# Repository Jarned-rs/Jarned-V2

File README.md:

# Jarned-V2
An improvement on the Jarned V1. A whole spilt keyboard with bluetooth!
I made it as a way to challenge myself after V1!

# Features
- 2 XIAO microcontrollers to control both sides
- 40 Keys!
- Bluetooth connectivity
- An open concept case to be able to marvel at the raw PCB
- 40 Diodes
- ZMK firmware to connect the two

# Photos!

# BOM
| Item | Qty | Supplier | Cost/item | Total cost | Link |
|---|---|---|---|---|---|
| XIAO nRF52840 | 2 | AliExpress | $9.10 | $18.20 | [Link](https://www.aliexpress.com/item/1005006988954136.html) |
| Key switches x 50 | 1 | AliExpress | $8.46 | $8.46 | [Link](https://www.aliexpress.com/item/1005007248231452.html) |
| Pin headers | 1 | AliExpress | $0.14 | $0.14 | [Link](https://www.aliexpress.com/item/1005006988954136.html) |
| LiPo battery | 2 | AliExpress | $2.41 | $4.82 | [Link](https://www.aliexpress.com/item/1005012703947199.html) |
| 50 keycaps | 1 | AliExpress | $7.49 | $7.49 | [Link](https://www.aliexpress.com/item/1005008827240220.html) |
| 3D printed case | 1 | A friend | $5.00 | $5.00 ||
| PCB | 1 | JLCPCB | $2.10 | $2.10 | [Link](https://cart.jlcpcb.com/shopcart/cart/) |
| Diodes | 50 | AliExpress | $1.72 | $1.72 | [Link]([https://cart.jlcpcb.com/shopcart/cart/](https://www.aliexpress.com/item/1005008818185494.html?spm=a2g0o.cart.0.0.37eb38daSEHkS9&mp=1)) |
| Estimated total shipping | 1 | | | $12.69 | |
| **Total** | | | | **$58.90** | |

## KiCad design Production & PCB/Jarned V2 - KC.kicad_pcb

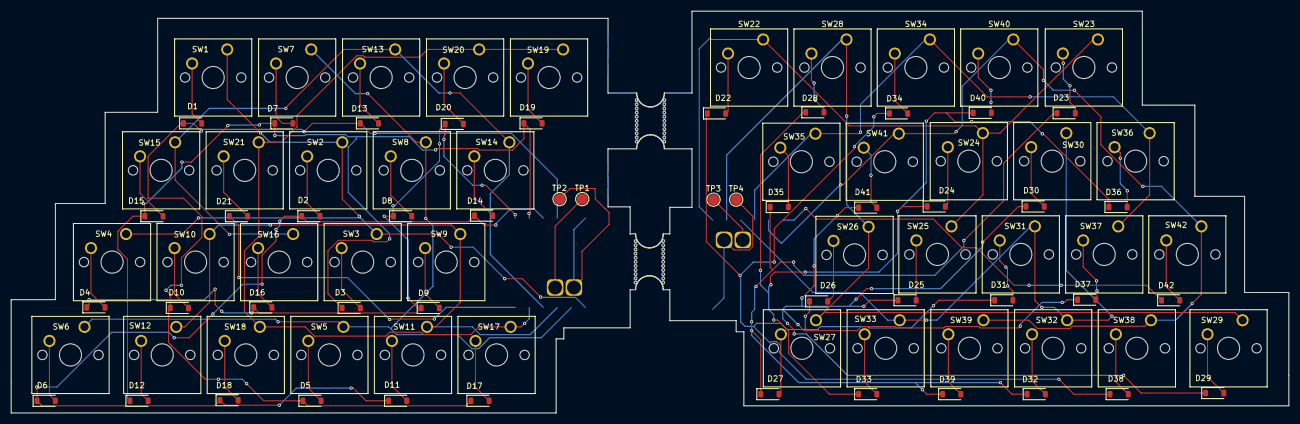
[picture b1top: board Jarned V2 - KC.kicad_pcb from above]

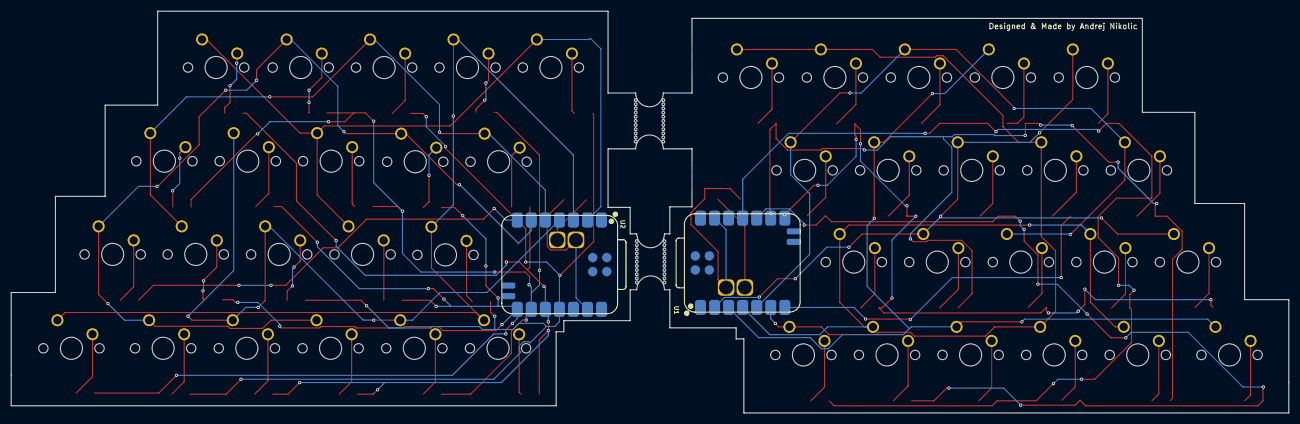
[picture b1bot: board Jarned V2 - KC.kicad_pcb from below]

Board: 2 copper layers, 231.2 x 72.7 mm, 92 parts (2 on the bottom side), 65 nets.

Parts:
D1, D2, D3, D4, D5, D6, D7, D8, D9, D10, D11, D12, D13, D14, D15, D16, D17, D18, D19, D20, D21, D22, D23, D24, D25, D26, D27, D28, D29, D30, D31, D32, D33, D34, D35, D36, D37, D38, D39, D40, D41, D42: D; D_SOD-123
H1, H5: MountingHole; mouse-bite-5mm-slot
SW1, SW2, SW3, SW4, SW5, SW6, SW7, SW8, SW9, SW10, SW11, SW12, SW13, SW14, SW15, SW16, SW17, SW18, SW19, SW20, SW21, SW22, SW23, SW24, SW25, SW26, SW27, SW28, SW29, SW30, SW31, SW32, SW33, SW34, SW35, SW36, SW37, SW38, SW39, SW40, SW41, SW42: SW_Push; SW_Cherry_MX_1.00u_PCB
TP1, TP3: BAT; TestPoint_Pad_D2.0mm
TP2, TP4: TestPoint; TestPoint_Pad_D2.0mm
U1, U2: XIAO-nRF52840-SMD; modified-XIAO-nRF52840-SMD

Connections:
/Left/COL0: SW1.1, SW2.1, SW3.1, SW4.1, U1.2 (P0.03_A1_D1)
/Left/COL1: SW5.1, SW6.1, SW7.1, SW8.1, U1.3 (P0.28_A2_D2)
/Left/COL2: SW9.1, SW10.1, SW11.1, SW12.1, U1.4 (P0.29_A3_D3)
/Left/COL3: SW13.1, SW14.1, SW15.1, SW16.1, U1.5 (P0.04_A4_D4_SDA)
/Left/COL4: SW17.1, SW18.1, SW19.1, SW20.1, SW21.1, U1.6 (P0.05_A5_D5_SCL)
/Left/ROW0: D1.1 (K), D5.1 (K), D10.1 (K), D13.1 (K), D17.1 (K), U1.11 (P1.15_D10_MOSI)
/Left/ROW1: D2.1 (K), D6.1 (K), D11.1 (K), D14.1 (K), D18.1 (K), U1.10 (P1.14_D9_MISO)
/Left/ROW2: D3.1 (K), D7.1 (K), D12.1 (K), D15.1 (K), D19.1 (K), U1.9 (P1.13_D8_SCK)
/Left/ROW3: D4.1 (K), D8.1 (K), D9.1 (K), D16.1 (K), D20.1 (K), U1.8 (P1.12_D7_RX)
/Left/ROW4: D21.1 (K), U1.7 (P1.11_D6_TX)
/Left/VBAT: TP1.1 (1_1), U1.15 (BAT)
/Right/COL0: SW22.1, SW23.1, SW24.1, SW25.1, U2.2 (P0.03_A1_D1)
/Right/COL1: SW26.1, SW27.1, SW28.1, SW29.1, U2.3 (P0.28_A2_D2)
/Right/COL2: SW30.1, SW31.1, SW32.1, SW33.1, U2.4 (P0.29_A3_D3)
/Right/COL3: SW34.1, SW35.1, SW36.1, SW37.1, U2.5 (P0.04_A4_D4_SDA)
/Right/COL4: SW38.1, SW39.1, SW40.1, SW41.1, SW42.1, U2.6 (P0.05_A5_D5_SCL)
/Right/ROW0: D22.1 (K), D26.1 (K), D31.1 (K), D34.1 (K), D38.1 (K), U2.11 (P1.15_D10_MOSI)
/Right/ROW1: D23.1 (K), D27.1 (K), D32.1 (K), D35.1 (K), D39.1 (K), U2.10 (P1.14_D9_MISO)
/Right/ROW2: D24.1 (K), D28.1 (K), D33.1 (K), D36.1 (K), D40.1 (K), U2.9 (P1.13_D8_SCK)
/Right/ROW3: D25.1 (K), D29.1 (K), D30.1 (K), D37.1 (K), D41.1 (K), U2.8 (P1.12_D7_RX)
/Right/ROW4: D42.1 (K), U2.7 (P1.11_D6_TX)
/Right/VBAT: TP3.1 (1_1), U2.15 (BAT)
GND: TP2.1 (1_1), TP4.1 (1_1), U1.13 (GND), U1.16 (GND), U2.13 (GND), U2.16 (GND)
unnamed: D1.2 (A), SW1.2
unnamed: D2.2 (A), SW2.2
unnamed: D3.2 (A), SW3.2
unnamed: D4.2 (A), SW4.2
unnamed: D5.2 (A), SW5.2
unnamed: D6.2 (A), SW6.2
unnamed: D7.2 (A), SW7.2
unnamed: D8.2 (A), SW8.2
unnamed: D9.2 (A), SW9.2
unnamed: D10.2 (A), SW10.2
unnamed: D11.2 (A), SW11.2
unnamed: D12.2 (A), SW12.2
unnamed: D13.2 (A), SW13.2
unnamed: D14.2 (A), SW14.2
unnamed: D15.2 (A), SW15.2
unnamed: D16.2 (A), SW16.2
unnamed: D17.2 (A), SW17.2
unnamed: D18.2 (A), SW18.2
unnamed: D19.2 (A), SW19.2
unnamed: D20.2 (A), SW20.2
unnamed: D21.2 (A), SW21.2
unnamed: D22.2 (A), SW22.2
unnamed: D23.2 (A), SW23.2
unnamed: D24.2 (A), SW24.2
unnamed: D25.2 (A), SW25.2
unnamed: D26.2 (A), SW26.2
unnamed: D27.2 (A), SW27.2
unnamed: D28.2 (A), SW28.2
unnamed: D29.2 (A), SW29.2
unnamed: D30.2 (A), SW30.2
unnamed: D31.2 (A), SW31.2
unnamed: D32.2 (A), SW32.2
unnamed: D33.2 (A), SW33.2
unnamed: D34.2 (A), SW34.2
unnamed: D35.2 (A), SW35.2
unnamed: D36.2 (A), SW36.2
unnamed: D37.2 (A), SW37.2
unnamed: D38.2 (A), SW38.2
unnamed: D39.2 (A), SW39.2
unnamed: D40.2 (A), SW40.2
unnamed: D41.2 (A), SW41.2
unnamed: D42.2 (A), SW42.2
